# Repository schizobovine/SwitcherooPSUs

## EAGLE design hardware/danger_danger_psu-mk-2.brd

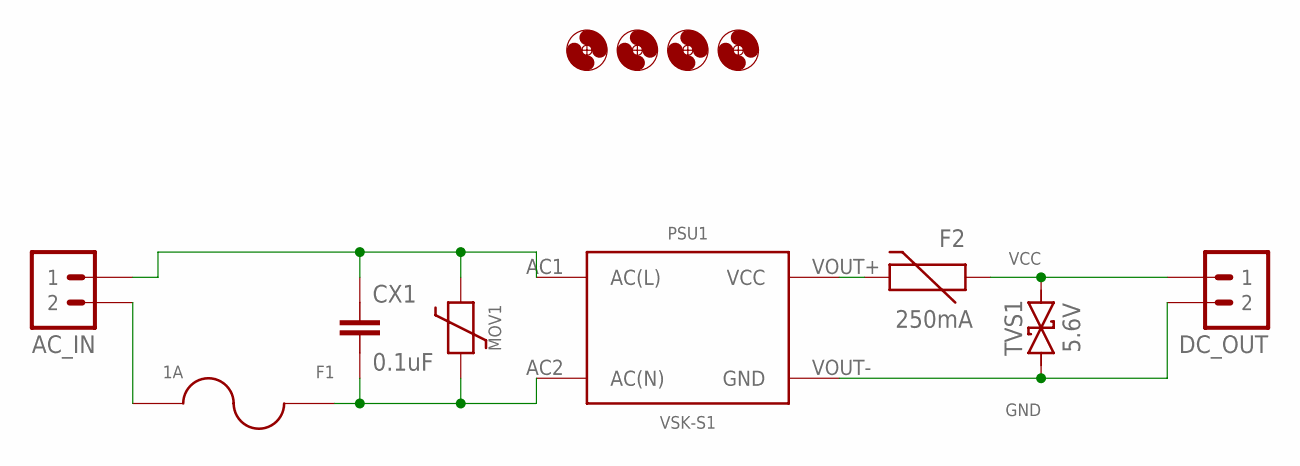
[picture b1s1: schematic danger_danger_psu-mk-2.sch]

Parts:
AC_IN: M023.5MM; SCREWTERMINAL-3.5MM-2
CX1: 0.1uF; XC10B5
DC_OUT: M02JST-PTH-VERT; JST-2-PH-VERT-PTH
F1: 1A; FUSE-2AG
F2: 250mA; PTC
H1, H2, H3, H4: HOLE#2; HOLE-#2
MOV1: VARISITORVAR-5.08MM-PTH; VAR-5.08MM-PTH
PSU1: VSK-S1
TVS1: 5.6V; DO-41-TVS-BI-10.16MM

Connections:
GND: DC_OUT.2, PSU1.VOUT- (GND), TVS1.P$2 (2)
unnamed: CX1.2, F1.1, F1.1@1 (1), MOV1.2, PSU1.AC2 (AC(N))
unnamed: AC_IN.1, CX1.1, MOV1.1, PSU1.AC1 (AC(L))
unnamed: AC_IN.2, F1.2, F1.2@2 (2)
unnamed: F2.P$2 (2), PSU1.VOUT+ (VCC)
VCC: DC_OUT.1, F2.P$1 (1), TVS1.P$1 (1)

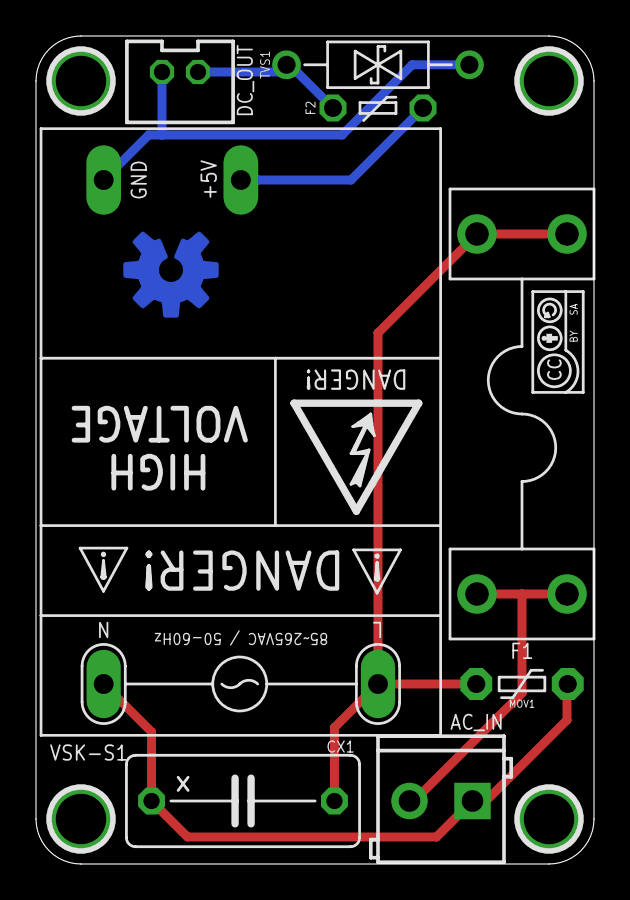
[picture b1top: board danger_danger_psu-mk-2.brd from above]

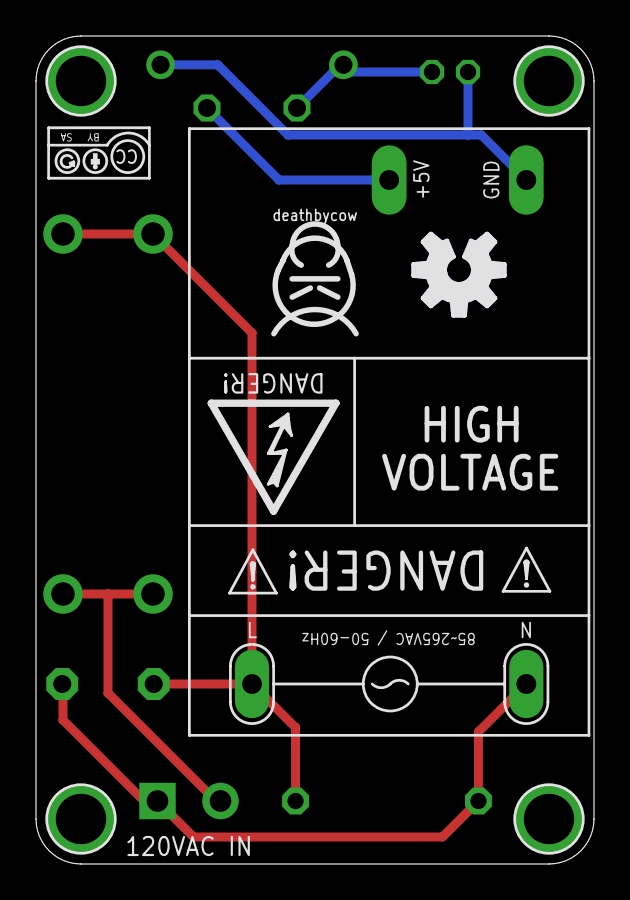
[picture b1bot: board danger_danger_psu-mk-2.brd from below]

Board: 2 copper layers, 31.0 x 46.0 mm, 16 parts (2 on the bottom side), 6 nets.

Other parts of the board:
U$1: COW_SMALL
U$2, U$3: CC-BY-SA-4.0-NO-URL
U$4: OSHWLOGO_BOT_0.2

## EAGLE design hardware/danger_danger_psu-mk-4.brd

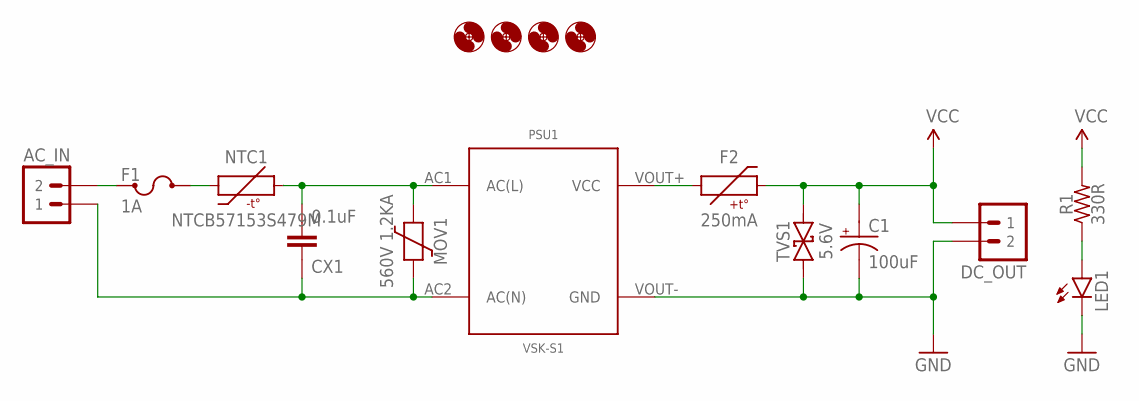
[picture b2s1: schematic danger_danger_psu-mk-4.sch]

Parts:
AC_IN: M023.5MM; SCREWTERMINAL-3.5MM-2
C1: 100uF; E2,5-6
CX1: 0.1uF; XC10B6
DC_OUT: M02JST-PTH-VERT; JST-2-PH-VERT-PTH
F1: 1A; TR5
F2: 250mA; PTC-PTH-5.08MM
H1, H2, H3, H4: HOLE#2; HOLE-#2
LED1: LED3MM
MOV1: 560V 1.2KA; VAR-5.08MM-PTH
NTC1: NTCB57153S479M; B57153S479M
PSU1: VSK-S1
R1: 330R; RESISTOR-AXIAL-PTH-5.08MM
TVS1: 5.6V; DO-41-TVS-BI-10.16MM

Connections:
GND: C1.-, DC_OUT.2, LED1.K (C), PSU1.VOUT- (GND), TVS1.P$2 (2)
unnamed: AC_IN.1, CX1.1, MOV1.2, PSU1.AC2 (AC(N))
unnamed: CX1.2, MOV1.1, NTC1.2, PSU1.AC1 (AC(L))
unnamed: AC_IN.2, F1.1
unnamed: LED1.A, R1.P$1 (1)
unnamed: F1.2, NTC1.1
unnamed: F2.P$1 (1), PSU1.VOUT+ (VCC)
VCC: C1.+, DC_OUT.1, F2.P$2 (2), R1.P$2 (2), TVS1.P$1 (1)

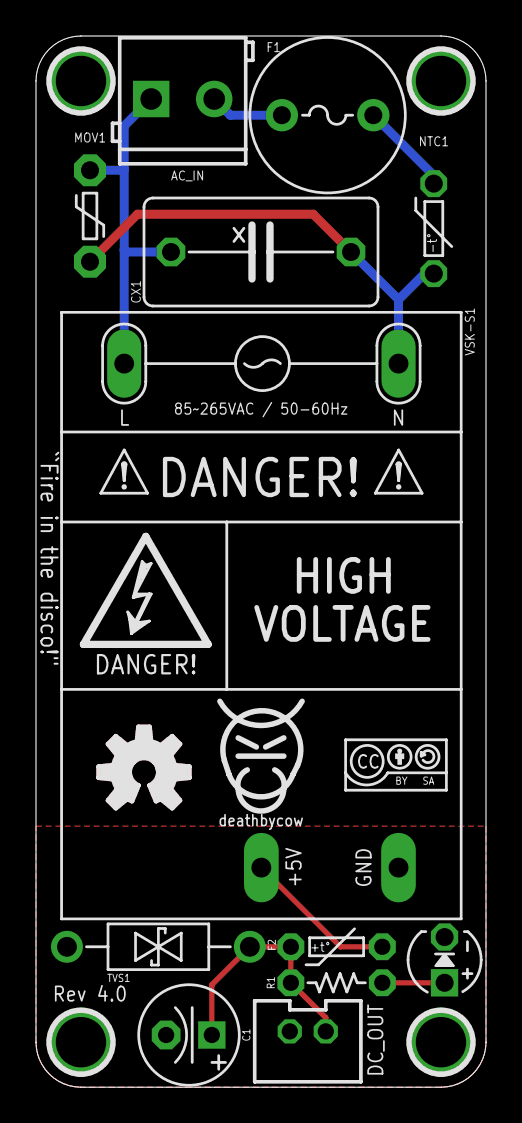
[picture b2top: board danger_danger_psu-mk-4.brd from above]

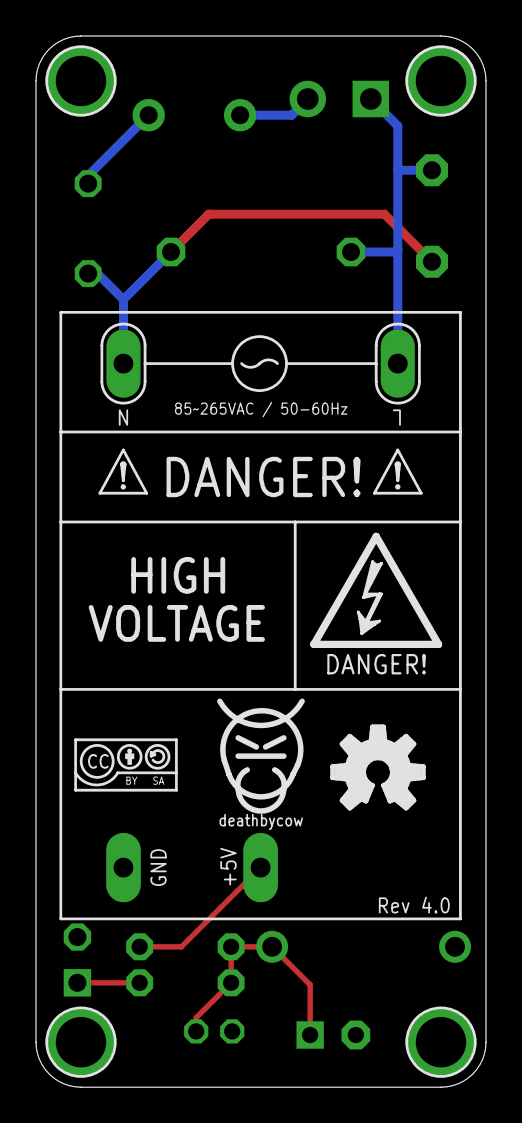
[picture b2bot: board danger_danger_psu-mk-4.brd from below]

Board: 2 copper layers, 25.0 x 58.4 mm, 22 parts (3 on the bottom side), 8 nets.

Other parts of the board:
U$1, U$6: COW_SMALL
U$3, U$7: CC-BY-SA-4.0-NO-URL
U$4, U$5: OSHWLOGO_BOT_0.2

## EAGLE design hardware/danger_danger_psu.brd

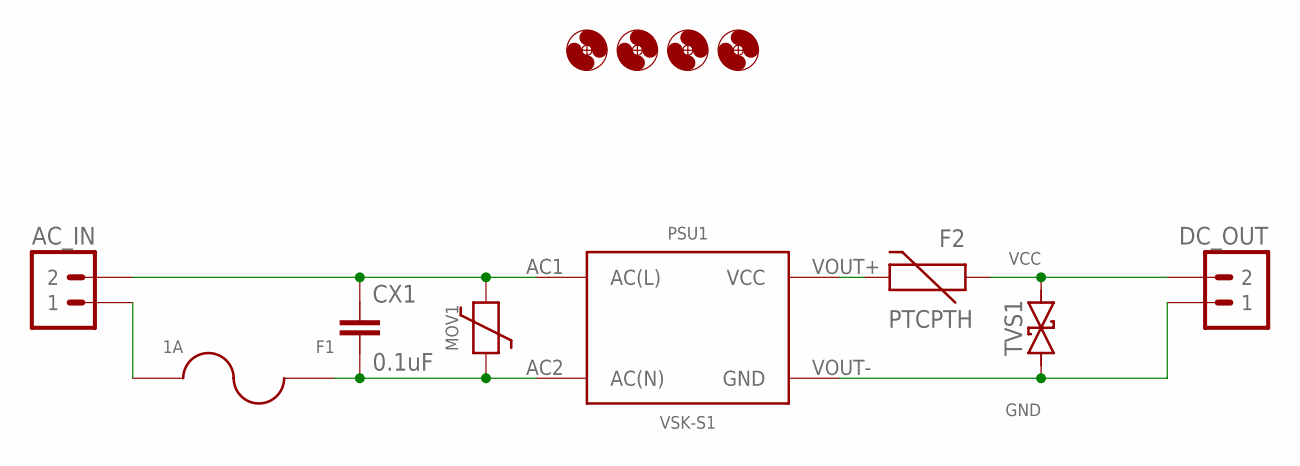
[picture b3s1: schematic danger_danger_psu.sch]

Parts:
AC_IN: M025MM; SCREWTERMINAL-5MM-2
CX1: 0.1uF; XC10B5
DC_OUT: M02JST-PTH-VERT; JST-2-PH-VERT-PTH
F1: 1A; FUSE-2AG
F2: PTCPTH; PTC
H1, H2, H3, H4: HOLE#4; HOLE-#4
MOV1: VARISITORVAR-5.08MM-PTH; VAR-5.08MM-PTH
PSU1: VSK-S1
TVS1: TVSDO-41-TVS-BIDIRECTIONAL; DO-41-TVS

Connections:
GND: DC_OUT.1, PSU1.VOUT- (GND), TVS1.P$2 (2)
unnamed: CX1.2, F1.1, F1.1@1 (1), MOV1.1, PSU1.AC2 (AC(N))
unnamed: AC_IN.2, CX1.1, MOV1.2, PSU1.AC1 (AC(L))
unnamed: AC_IN.1, F1.2, F1.2@2 (2)
unnamed: F2.P$2 (2), PSU1.VOUT+ (VCC)
VCC: DC_OUT.2, F2.P$1 (1), TVS1.P$1 (1)

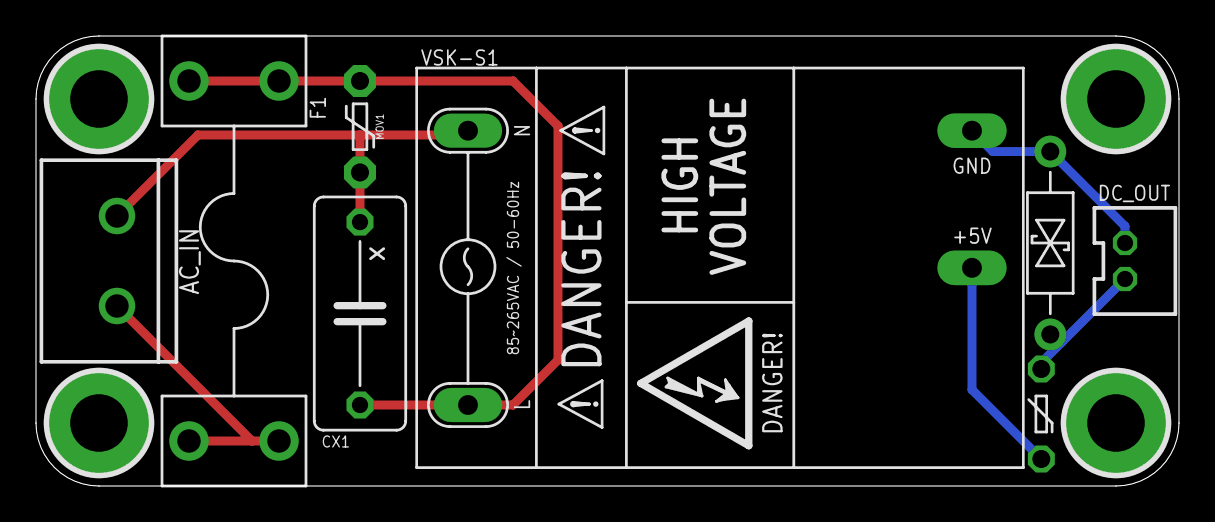
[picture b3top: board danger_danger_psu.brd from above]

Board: 2 copper layers, 63.5 x 25.0 mm, 12 parts (0 on the bottom side), 6 nets.

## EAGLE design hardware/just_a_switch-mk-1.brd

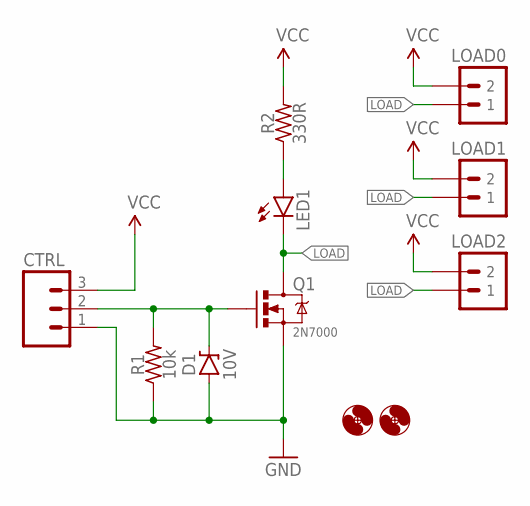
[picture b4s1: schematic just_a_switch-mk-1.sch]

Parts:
CTRL: M03PTH; 1X03
D1: 10V; DIODE-7.62MM
H1, H2: HOLE#2; HOLE-#2
LED1: LED3MM
LOAD0: M02PTH-2MM; 1X02-2MM-PTH
LOAD1: M021X02_NO_SILK; 1X02_NO_SILK
LOAD2: M023.5MM; SCREWTERMINAL-3.5MM-2
Q1: 2N7000; TO-92-AMMO
R1: 10k; RESISTOR-AXIAL-PTH-7.62MM
R2: 330R; RESISTOR-AXIAL-PTH-7.62MM

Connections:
GND: CTRL.1, D1.A, Q1.1 (S), R1.P$1 (1)
LOAD: LED1.K (C), LOAD0.P$1 (1), LOAD1.1, LOAD2.1, Q1.3 (D)
unnamed: CTRL.2, D1.K (C), Q1.2 (G), R1.P$2 (2)
unnamed: LED1.A, R2.P$1 (1)
VCC: CTRL.3, LOAD0.P$2 (2), LOAD1.2, LOAD2.2, R2.P$2 (2)

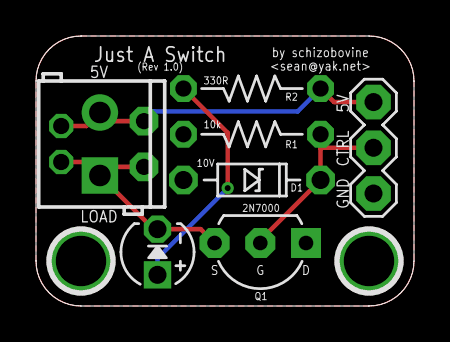
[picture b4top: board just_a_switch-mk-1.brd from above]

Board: 2 copper layers, 21.0 x 15.0 mm, 12 parts (1 on the bottom side), 5 nets.

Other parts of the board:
U$1: CC-BY-SA-4.0-NO-URL

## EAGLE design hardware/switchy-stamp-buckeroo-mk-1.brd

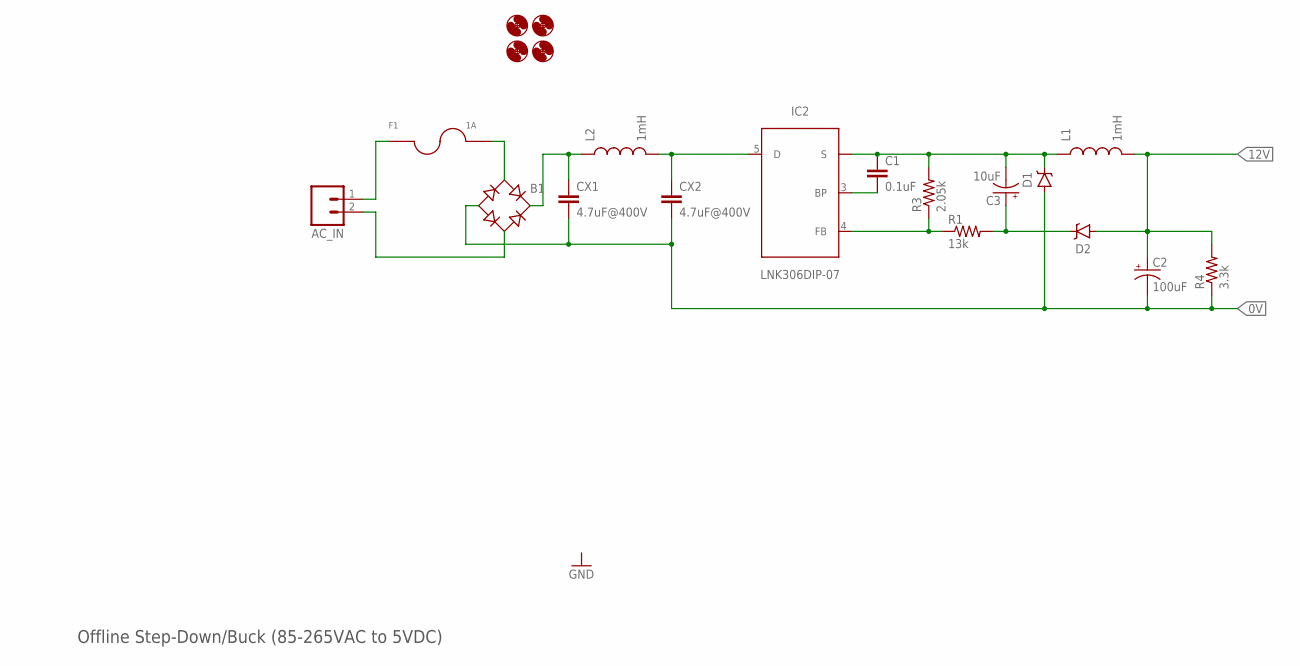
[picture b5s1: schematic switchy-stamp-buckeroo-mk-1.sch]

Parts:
AC_IN: M023.5MM; SCREWTERMINAL-3.5MM-2
B1: RB1ANOSUCK; RB1A-NOSUCK
C1: 0.1uF; C025-024X044
C2: 100uF; E3,5-8
C3: 10uF; E3,5-8
CX1, CX2: 4.7uF@400V; XC10B5
D1, D2: 1N5819; DIODE-10.16MM
F1: 1A; FUSE-2AG
H1, H2, H3, H4: HOLE#2; HOLE-#2
IC2: LNK306DIP-07; DIP-07
L1, L2: 1mH; INDUCTOR-AXIAL-PTH-10.16MM
R1: 13k; RESISTOR-AXIAL-PTH-6.35MM
R3: 2.05k; RESISTOR-AXIAL-PTH-6.35MM
R4: 3.3k; RESISTOR-AXIAL-PTH-6.35MM

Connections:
0V: B1.-, C2.-, CX1.2, CX2.2, D1.A, R4.P$1 (1)
12V: C2.+, D2.A, L1.P$2 (2), R4.P$2 (2)
unnamed: IC2.4 (FB), R1.P$1 (1), R3.P$1 (1)
unnamed: C3.+, D2.C, R1.P$2 (2)
unnamed: B1.AC1, F1.2, F1.2@2 (2)
unnamed: AC_IN.1, F1.1, F1.1@1 (1)
unnamed: B1.+, CX1.1, L2.P$1 (1)
unnamed: AC_IN.2, B1.AC2
unnamed: CX2.1, IC2.5 (D), L2.P$2 (2)
unnamed: C1.1, C3.-, D1.C, IC2.1 (S), IC2.2 (S), IC2.7 (S), IC2.8 (S), L1.P$1 (1), R3.P$2 (2)
unnamed: C1.2, IC2.3 (BP)

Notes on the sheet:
Offline Step-Down/Buck (85-265VAC to 5VDC)

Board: 2 copper layers, 22 parts (2 on the bottom side), 11 nets, no tracks yet.

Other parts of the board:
U$1: COW_SMALL
U$2: CC-BY-SA-4.0-NO-URL

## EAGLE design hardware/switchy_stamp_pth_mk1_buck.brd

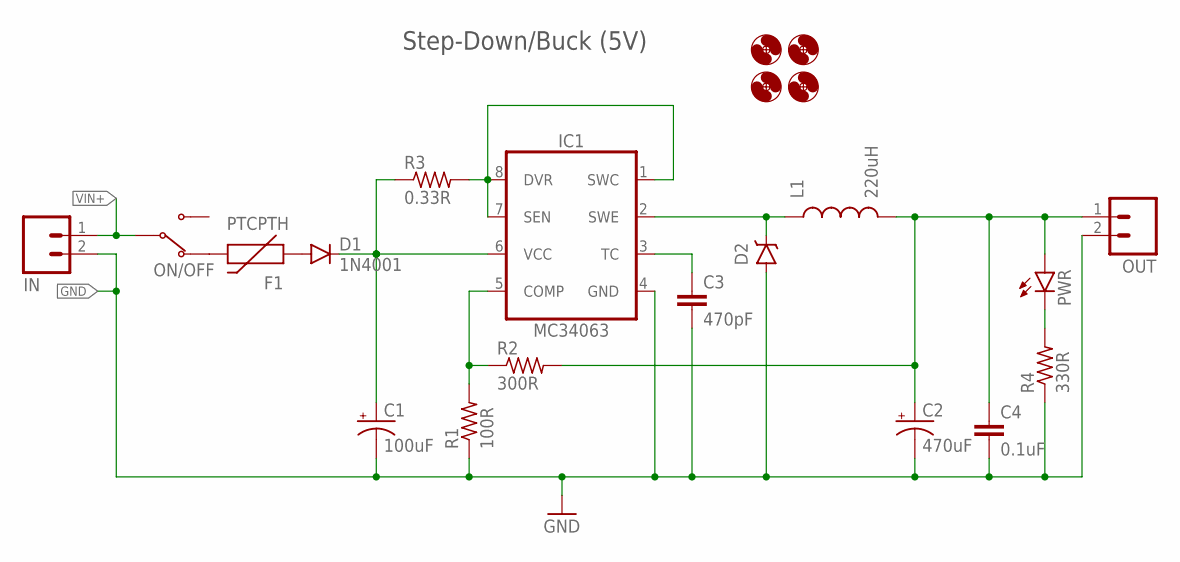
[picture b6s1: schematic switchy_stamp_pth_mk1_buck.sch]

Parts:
C1: 100uF; E2,5-7
C2: 470uF; E2,5-7
C3: 470pF; C025-024X044
C4: 0.1uF; C025-024X044
D1: 1N4001; DIODE-10.16MM
D2: 1N5819; DIODE-10.16MM
F1: PTCPTH; PTC
H1, H2, H3, H4: HOLE#2; HOLE-#2
IC1: MC34063; DIP-08
IN: M02JST-PTH-2; JST-2-PH-RA-PTH
L1: 220uH; RADIAL-PTH-6MMDIA
ON/OFF: SWITCH-SPDTSSA-12; SWITCH-SPDT-SSA-12
OUT: M02JST-PTH-2; JST-2-PH-RA-PTH
PWR: LED3MM
R1: 100R; RESISTOR-AXIAL-PTH-5.08MM
R2: 300R; RESISTOR-AXIAL-PTH-5.08MM
R3: 0.33R; RESISTOR-AXIAL-PTH-10.16MM
R4: 330R; RESISTOR-AXIAL-PTH-5.08MM

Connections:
GND: C1.-, C2.-, C3.2, C4.2, D2.A, IC1.4 (GND), IN.2, OUT.2, R1.P$1 (1), R4.P$1 (1)
unnamed: IC1.1 (SWC), IC1.7 (SEN), IC1.8 (DVR), R3.P$2 (2)
unnamed: C3.1, IC1.3 (TC)
unnamed: IC1.5 (COMP), R1.P$2 (2), R2.P$1 (1)
unnamed: D1.A, F1.P$1 (1)
unnamed: C1.+, D1.C, IC1.6 (VCC), R3.P$1 (1)
unnamed: D2.C, IC1.2 (SWE), L1.1
unnamed: PWR.K (C), R4.P$2 (2)
unnamed: F1.P$2 (2), ON/OFF.A (NC)
VIN+: IN.1, ON/OFF.COM
VOUT-: C2.+, C4.1, L1.2, OUT.1, PWR.A, R2.P$2 (2)

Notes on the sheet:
Step-Down/Buck (5V)

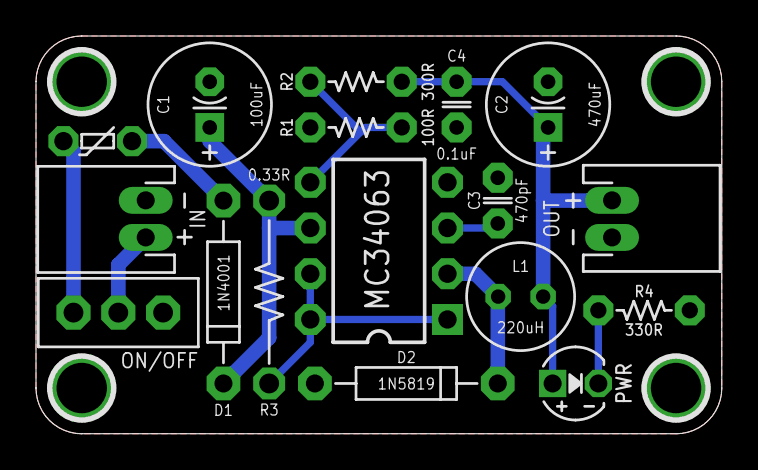
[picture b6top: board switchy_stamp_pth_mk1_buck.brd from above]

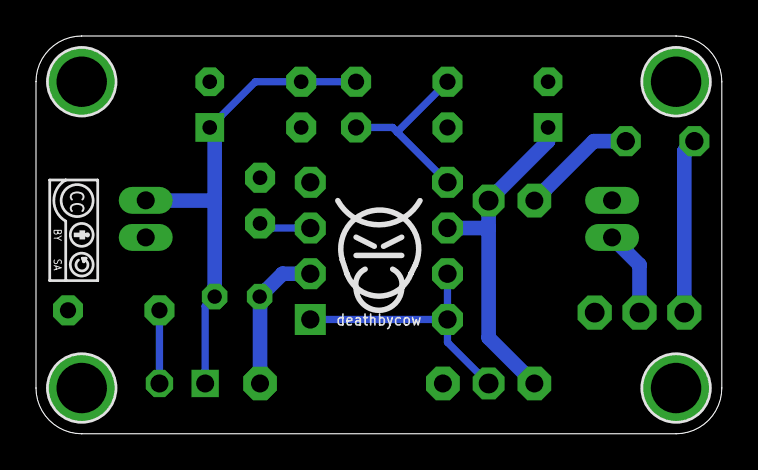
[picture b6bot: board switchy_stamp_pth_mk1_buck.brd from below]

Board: 2 copper layers, 38.1 x 22.1 mm, 23 parts (2 on the bottom side), 11 nets.

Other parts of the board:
U$1: COW_SMALL
U$2: CC-BY-SA-4.0-NO-URL

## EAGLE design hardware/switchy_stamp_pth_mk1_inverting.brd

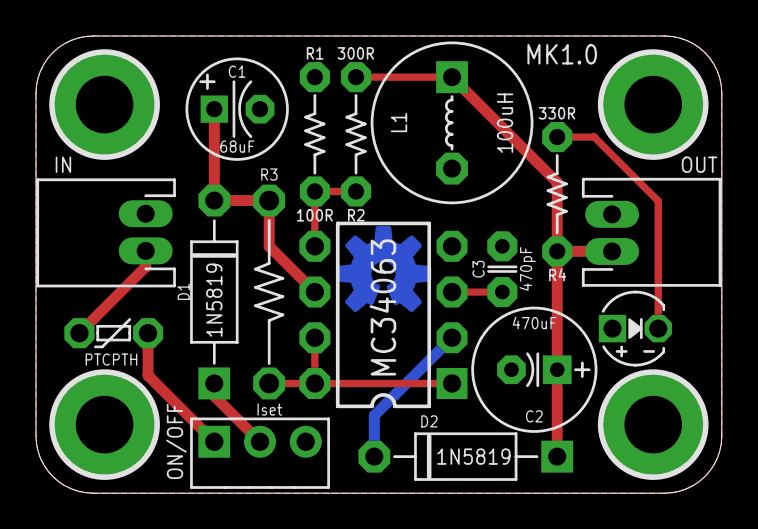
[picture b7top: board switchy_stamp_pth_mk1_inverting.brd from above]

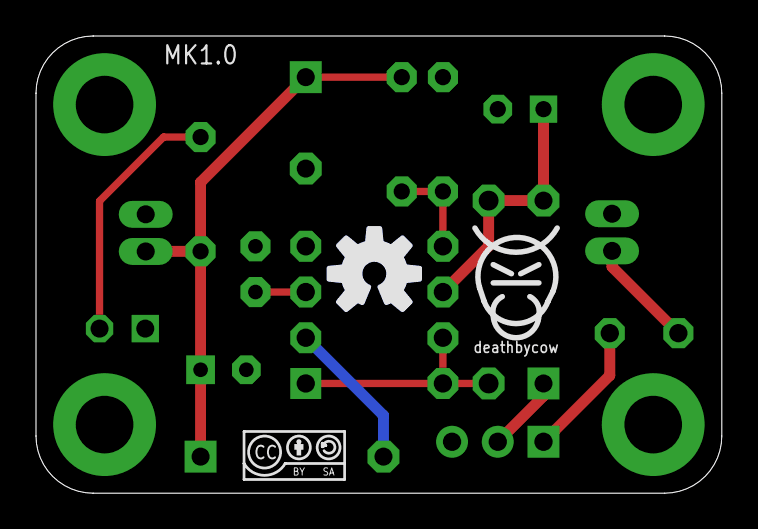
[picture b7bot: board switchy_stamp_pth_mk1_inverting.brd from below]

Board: 2 copper layers, 38.1 x 25.4 mm, 23 parts (2 on the bottom side), 11 nets.

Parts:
C1: 68uF; E2,5-6
C2: 470uF; E2,5-7
C3: 470pF; C025-024X044
D1, D2: 1N5819; DO-41
F1: PTCPTH; PTC
H1, H2, H3, H4: HOLE#4; HOLE-#4
IC1: MC34063; DIP-08
IN: M02JST-PTH-2; JST-2-PTH
L1: 100uH; RLB0912
LED1: LED3MM
ON/OFF: SWITCH-SPDTPTH-RA-2.54MM; SPDT-RA-2.54MM
OUT: M02JST-PTH-2; JST-2-PTH
R1: 100R; RESISTOR-AXIAL-PTH-5.08MM
R2: 300R; RESISTOR-AXIAL-PTH-5.08MM
R3: Iset; RESISTOR-AXIAL-PTH-10.16MM
R4: 330R; RESISTOR-AXIAL-PTH-5.08MM
U$1: CC-BY-SA-4.0-NO-URL
U$2: COW_SMALL
U$3: OSHWLOGO_BOT_0.2_A

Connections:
GND: C1.-, C2.-, C3.2, IC1.4, IN.2, L1.2, LED1.A, OUT.1, R1.P$1
unnamed: IC1.1, IC1.7, IC1.8, R3.P$2
unnamed: C3.1, IC1.3
unnamed: IC1.5, R1.P$2, R2.P$1
unnamed: D1.A, ON/OFF.2
unnamed: C1.+, D1.C, IC1.6, R3.P$1
unnamed: D2.C, IC1.2
unnamed: LED1.K, R4.P$2
unnamed: F1.P$1, ON/OFF.1
VIN+: F1.P$2, IN.1
VOUT-: C2.+, D2.A, L1.1, OUT.2, R2.P$2, R4.P$1
